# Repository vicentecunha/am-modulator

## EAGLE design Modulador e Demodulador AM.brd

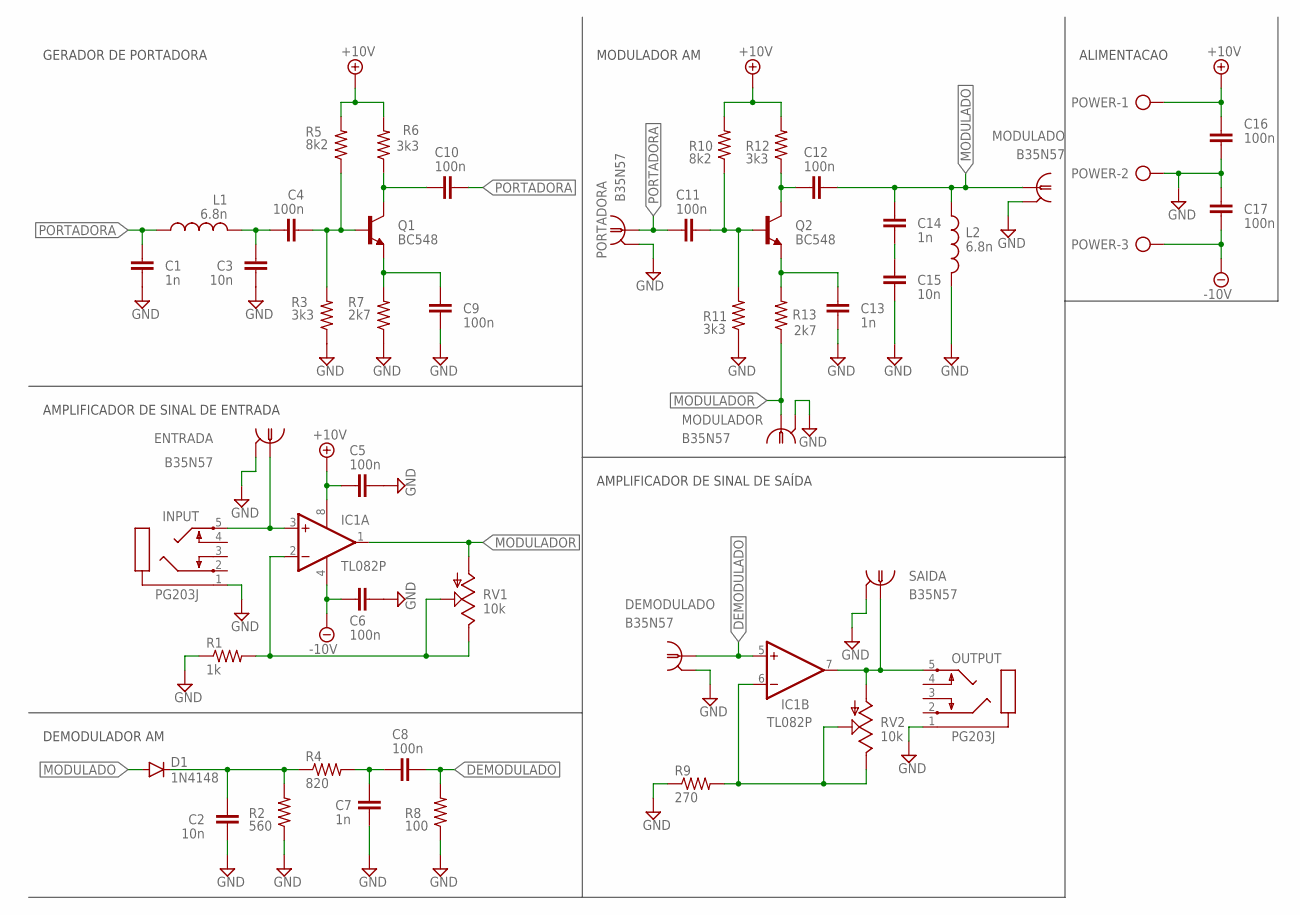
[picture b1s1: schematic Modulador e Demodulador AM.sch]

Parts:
C1, C7, C13, C14: 1n; CAP-PTH-SMALL2
C2, C3, C15: 10n; CAP-PTH-SMALL2
C4, C5, C6, C8, C9, C10, C11, C12, C16, C17: 100n; CAP-PTH-SMALL2
D1: 1N4148; DIODE-1N4148
DEMODULADO: B35N57
ENTRADA: B35N57
IC1: TL082P; DIL08
INPUT: PG203J
L1, L2: 6.8n; 0207/10
MODULADO: B35N57
MODULADOR: B35N57
OUTPUT: PG203J
PORTADORA: B35N57
POWER: AK500/3-H
Q1, Q2: BC548; TO92-EBC
R1: 1k; AXIAL-0.3
R2: 560; AXIAL-0.3
R3, R6, R11, R12: 3k3; AXIAL-0.3
R4: 820; AXIAL-0.3
R5, R10: 8k2; AXIAL-0.3
R7, R13: 2k7; AXIAL-0.3
R8: 100; AXIAL-0.3
R9: 270; AXIAL-0.3
RV1, RV2: 10k; POT_ALPHA_RV16AF-20
SAIDA: B35N57

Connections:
+10V: C5.1, C16.1, IC1.8 (V+), POWER.1, R5.P$2 (2), R6.P$2 (2), R10.P$2 (2), R12.P$2 (2)
-10V: C6.1, C17.2, IC1.4 (V-), POWER.3
DEMODULADO: C8.2, DEMODULADO.1, IC1.5 (+IN), R8.P$2 (2)
GND: C1.2, C2.2, C3.2, C5.2, C6.2, C7.2, C9.2, C13.2, C15.2, C16.2, C17.1, DEMODULADO.2, DEMODULADO.3 (2), DEMODULADO.4 (2), DEMODULADO.5 (2), ENTRADA.2, ENTRADA.3 (2), ENTRADA.4 (2), ENTRADA.5 (2), INPUT.1, L2.2, MODULADO.2, MODULADO.3 (2), MODULADO.4 (2), MODULADO.5 (2), MODULADOR.2, MODULADOR.3 (2), MODULADOR.4 (2), MODULADOR.5 (2), OUTPUT.1, PORTADORA.2, PORTADORA.3 (2), PORTADORA.4 (2), PORTADORA.5 (2), POWER.2, R1.P$1 (1), R2.P$1 (1), R3.P$1 (1), R7.P$1 (1), R8.P$1 (1), R9.P$1 (1), R11.P$1 (1), SAIDA.2, SAIDA.3 (2), SAIDA.4 (2), SAIDA.5 (2)
MODULADO: C12.2, C14.1, D1.A, L2.1, MODULADO.1
MODULADOR: IC1.1 (OUT), MODULADOR.1, R13.P$1 (1), RV1.1 (A)
unnamed: C11.2, Q2.B, R10.P$1 (1), R11.P$2 (2)
unnamed: IC1.2 (-IN), R1.P$2 (2), RV1.2 (S), RV1.3 (E)
unnamed: C9.1, Q1.E, R7.P$2 (2)
unnamed: C4.2, Q1.B, R3.P$2 (2), R5.P$1 (1)
unnamed: C10.1, Q1.C, R6.P$1 (1)
unnamed: IC1.6 (-IN), R9.P$2 (2), RV2.2 (S), RV2.3 (E)
unnamed: C12.1, Q2.C, R12.P$1 (1)
unnamed: ENTRADA.1, IC1.3 (+IN), INPUT.5
unnamed: C13.1, Q2.E, R13.P$2 (2)
unnamed: C3.1, C4.1, L1.2
unnamed: C14.2, C15.1
unnamed: C2.1, D1.C, R2.P$2 (2), R4.P$1 (1)
unnamed: C7.1, C8.1, R4.P$2 (2)
unnamed: IC1.7 (OUT), OUTPUT.5, RV2.1 (A), SAIDA.1
PORTADORA: C1.1, C10.2, C11.1, L1.1, PORTADORA.1

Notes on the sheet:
GERADOR DE PORTADORA
MODULADOR AM
AMPLIFICADOR DE SINAL DE ENTRADA
DEMODULADOR AM
AMPLIFICADOR DE SINAL DE SAÍDA
ALIMENTACAO

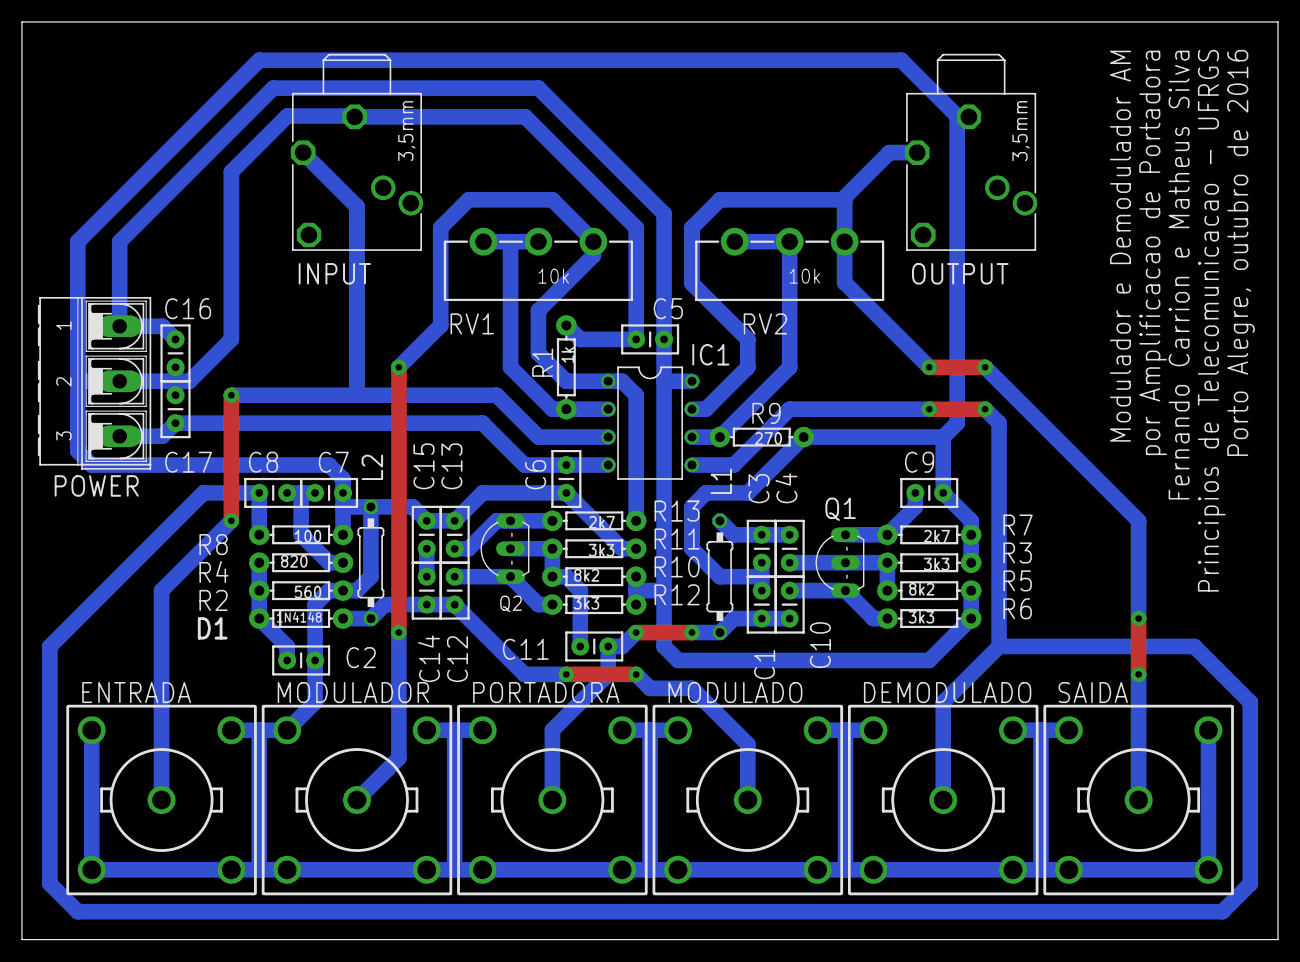
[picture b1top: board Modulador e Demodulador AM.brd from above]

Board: 2 copper layers, 114.3 x 83.5 mm, 47 parts (0 on the bottom side), 21 nets.

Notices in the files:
parts and their libraries:
SparkFun-Capacitors: Licensing: Creative Commons ShareAlike 4.0 International - https://creativecommons.org/licenses/by-sa/4.0
